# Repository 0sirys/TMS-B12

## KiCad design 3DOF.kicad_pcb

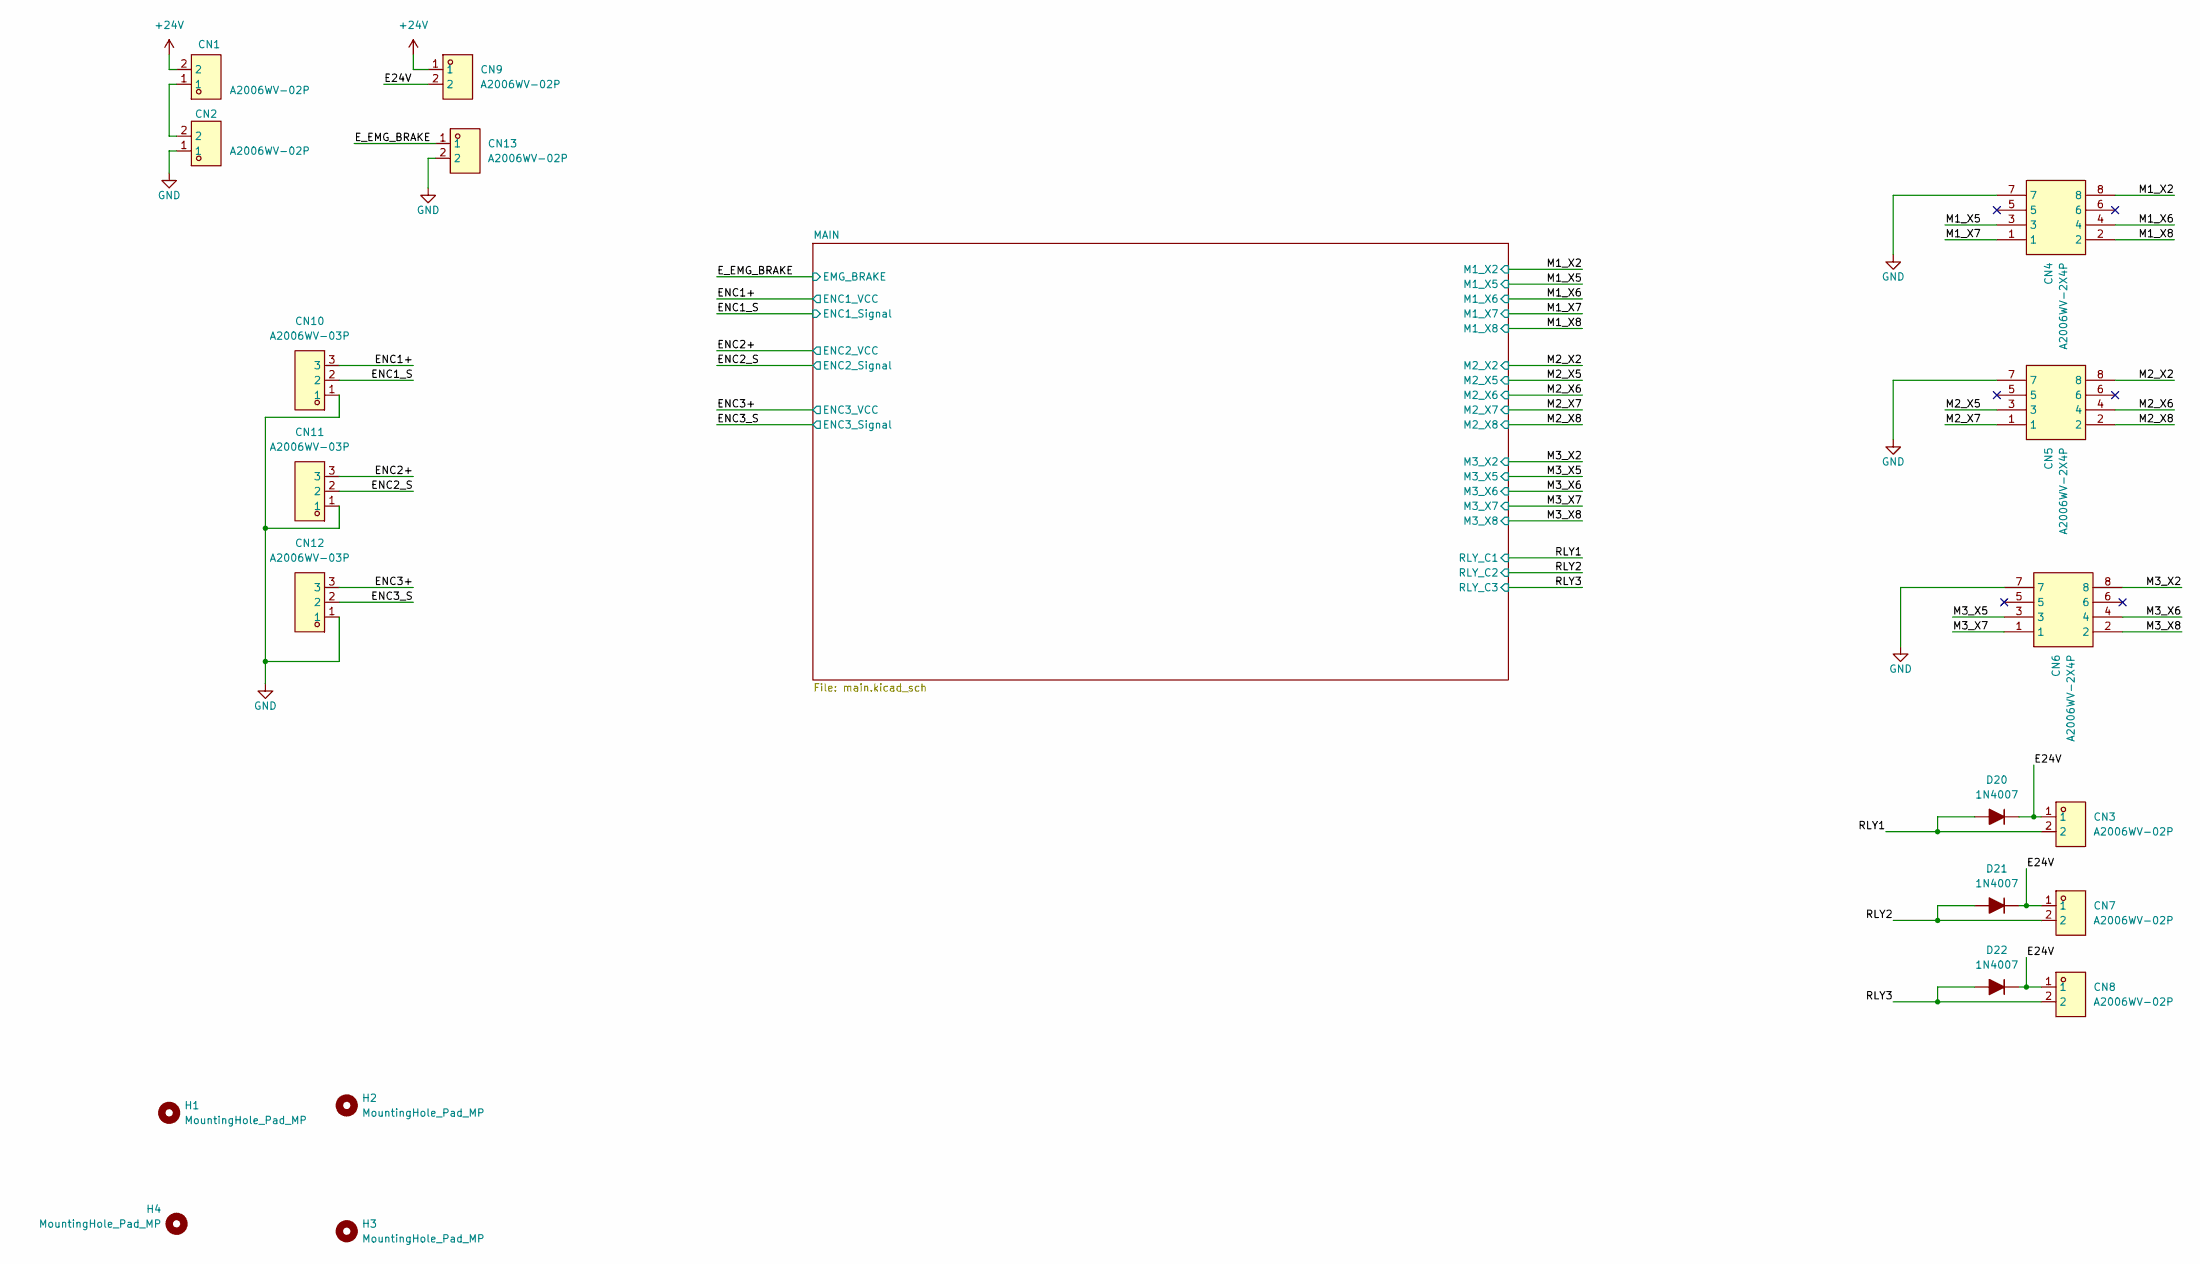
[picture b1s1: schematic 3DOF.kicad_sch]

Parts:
CN1, CN2, CN3, CN7, CN8, CN9, CN13: A2006WV-02P; CONN-TH_2P-P2.00_A2006WV-02P; MPN A2006WV-02P; LCSC Part C465363
CN4, CN5, CN6: A2006WV-2X4P; CONN-TH_A2006WV-2X4P; MPN A2006WV-2x4P; LCSC Part C225315
CN10, CN11, CN12: A2006WV-03P; CONN-TH_3P-P2.00_A2006WV-03P; MPN A2006WV-03P; LCSC Part C465364
D20, D21, D22: 1N4007; D_DO-41_SOD81_P7.62mm_Horizontal; LCSC Part C19357
H1, H2, H3, H4: MountingHole_Pad_MP; MountingHole_2.5mm

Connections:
+24V: CN1.2, CN9.1; also elsewhere on the board
/E24V: CN3.1, CN7.1, CN8.1, CN9.2, D20.1 (K), D21.1 (K), D22.1 (K)
/ENC1+: CN10.3; also elsewhere on the board
/ENC1_S: CN10.2; also elsewhere on the board
/ENC2+: CN11.3; also elsewhere on the board
/ENC2_S: CN11.2; also elsewhere on the board
/ENC3+: CN12.3; also elsewhere on the board
/ENC3_S: CN12.2; also elsewhere on the board
/E_EMG_BRAKE: CN13.1; also elsewhere on the board
/M1_X2: CN4.8; also elsewhere on the board
/M1_X5: CN4.3; also elsewhere on the board
/M1_X6: CN4.4; also elsewhere on the board
/M1_X7: CN4.1; also elsewhere on the board
/M1_X8: CN4.2; also elsewhere on the board
/M2_X2: CN5.8; also elsewhere on the board
/M2_X5: CN5.3; also elsewhere on the board
/M2_X6: CN5.4; also elsewhere on the board
/M2_X7: CN5.1; also elsewhere on the board
/M2_X8: CN5.2; also elsewhere on the board
/M3_X2: CN6.8; also elsewhere on the board
/M3_X5: CN6.3; also elsewhere on the board
/M3_X6: CN6.4; also elsewhere on the board
/M3_X7: CN6.1; also elsewhere on the board
/M3_X8: CN6.2; also elsewhere on the board
/RLY1: CN3.2, D20.2 (A); also elsewhere on the board
/RLY2: CN7.2, D21.2 (A); also elsewhere on the board
/RLY3: CN8.2, D22.2 (A); also elsewhere on the board
GND: CN2.1, CN4.7, CN5.7, CN6.7, CN10.1, CN11.1, CN12.1, CN13.2; also elsewhere on the board
unnamed: CN1.1, CN2.2

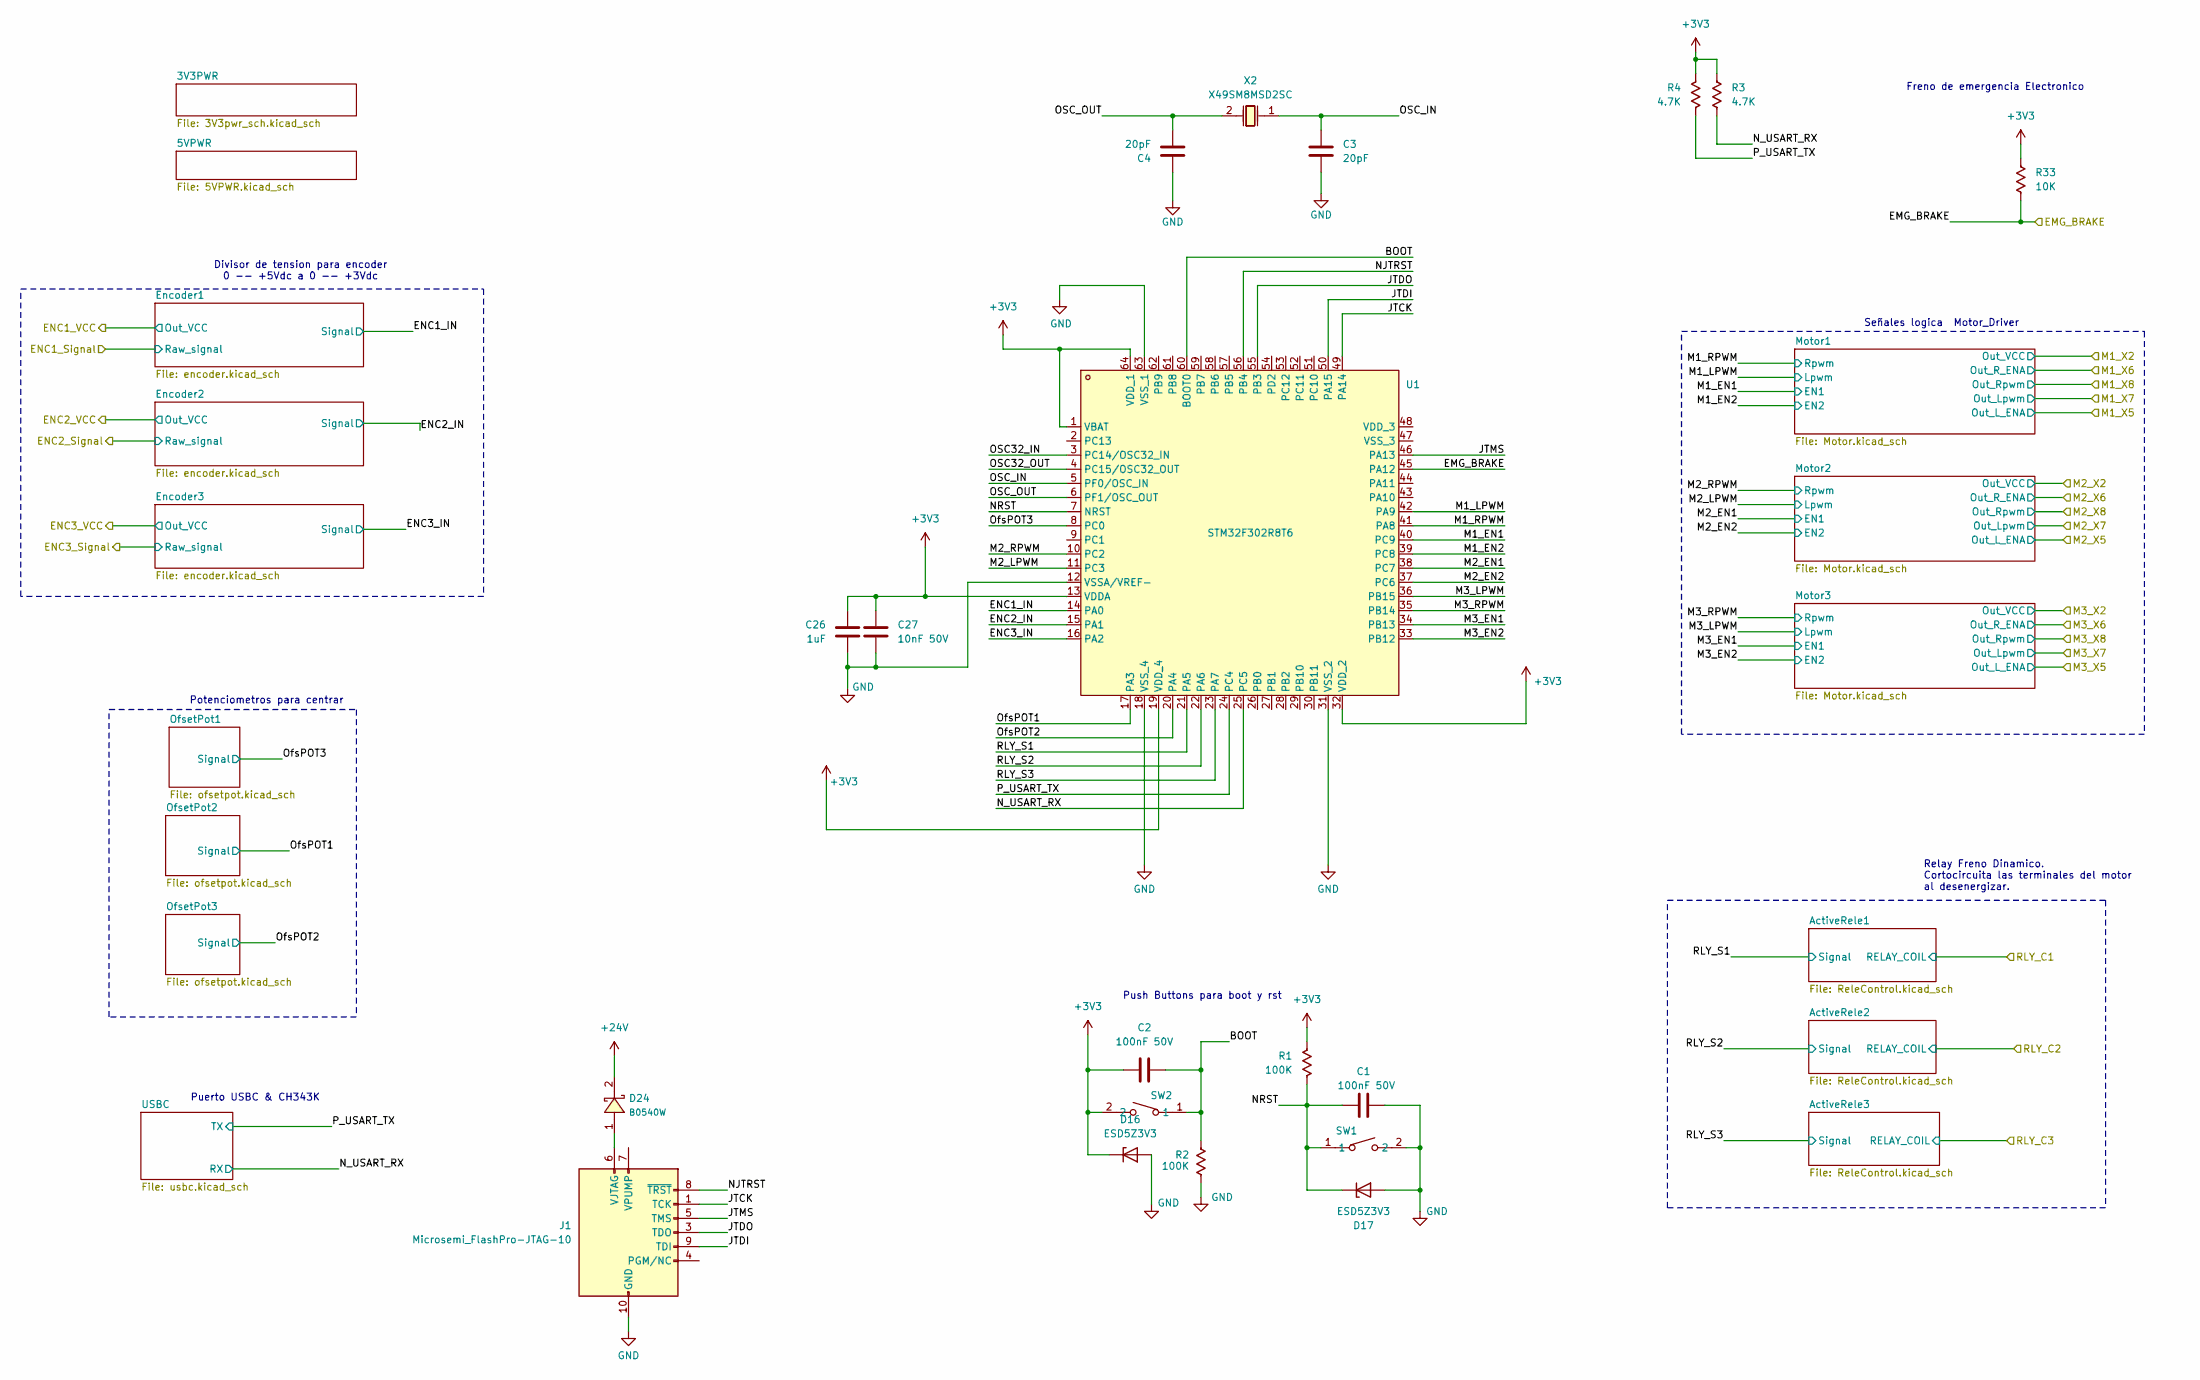
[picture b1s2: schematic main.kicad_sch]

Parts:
C1, C2: 100nF 50V; C_0402_1005Metric; LCSC Part C307331
C3, C4: 20pF; C_0402_1005Metric; LCSC Part C1554
C26: 1uF; C_0402_1005Metric; LCSC Part C52923
C27: 10nF 50V; C_0402_1005Metric; LCSC Part C1524
D16, D17: ESD5Z3V3; D_SOD-523; LCSC Part C502545
D24: B0540W; SOD-123_L2.7-W1.6-LS3.7-FD; MPN B0540W; LCSC Part C7420325
J1: Microsemi_FlashPro-JTAG-10; IDC-Header_2x05_P2.54mm_Vertical; LCSC Part C53207564
R1, R2: 100K; R_0402_1005Metric; LCSC Part C25741
R3, R4: 4.7K; R_0402_1005Metric; LCSC Part C25900
R33: 10K; R_0402_1005Metric; LCSC Part C25744
SW1, SW2: TS-1088-AR02016; SW-SMD_L3.9-W3.0-P4.45; MPN TS-1088-AR02016; LCSC Part C720477
U1: STM32F302R8T6; QFP-64_L10.0-W10.0-P0.50-LS12.0-BL; MPN STM32F302R8T6; LCSC Part C504601
X2: X49SM8MSD2SC; CRYSTAL-SMD_L11.5-W4.8-LS12.7; MPN X49SM8MSD2SC; LCSC Part C12674

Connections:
+3V3: C2.2, C26.1, C27.1, D16.1 (K), R1.1, R3.1, R4.1, R33.1, SW2.2, U1.1 (VBAT), U1.13 (VDDA), U1.19 (VDD_4), U1.32 (VDD_2), U1.64 (VDD_1); also elsewhere on the board
+24V: D24.2; also elsewhere on the board
/E_EMG_BRAKE: R33.2, U1.45 (PA12); also elsewhere on the board
/M1_X5: U1.39 (PC8); also elsewhere on the board
/M1_X6: U1.40 (PC9); also elsewhere on the board
/M1_X7: U1.42 (PA9); also elsewhere on the board
/M1_X8: U1.41 (PA8); also elsewhere on the board
/M2_X5: U1.37 (PC6); also elsewhere on the board
/M2_X6: U1.38 (PC7); also elsewhere on the board
/M2_X7: U1.11 (PC3); also elsewhere on the board
/M2_X8: U1.10 (PC2); also elsewhere on the board
/M3_X5: U1.33 (PB12); also elsewhere on the board
/M3_X6: U1.34 (PB13); also elsewhere on the board
/M3_X7: U1.36 (PB15); also elsewhere on the board
/M3_X8: U1.35 (PB14); also elsewhere on the board
/MAIN/BOOT: C2.1, R2.2, SW2.1, U1.60 (BOOT0)
/MAIN/ENC1_IN: U1.14 (PA0); also elsewhere on the board
/MAIN/ENC2_IN: U1.15 (PA1); also elsewhere on the board
/MAIN/ENC3_IN: U1.16 (PA2); also elsewhere on the board
/MAIN/JTCK: J1.1 (TCK), U1.49 (PA14)
/MAIN/JTDI: J1.9 (TDI), U1.50 (PA15)
/MAIN/JTDO: J1.3 (TDO), U1.55 (PB3)
/MAIN/JTMS: J1.5 (TMS), U1.46 (PA13)
/MAIN/NJTRST: J1.8 (~TRST), U1.56 (PB4)
/MAIN/NRST: C1.1, D17.1 (K), R1.2, SW1.1, U1.7 (NRST)
/MAIN/N_USART_RX: R3.2, U1.25 (PC5); also elsewhere on the board
/MAIN/OSC32_IN: U1.3 (PC14/OSC32_IN)
/MAIN/OSC32_OUT: U1.4 (PC15/OSC32_OUT)
/MAIN/OSC_IN: C3.2, U1.5 (PF0/OSC_IN), X2.1
/MAIN/OSC_OUT: C4.2, U1.6 (PF1/OSC_OUT), X2.2
/MAIN/OfsPOT1: U1.17 (PA3); also elsewhere on the board
/MAIN/OfsPOT2: U1.20 (PA4); also elsewhere on the board
/MAIN/OfsPOT3: U1.8 (PC0); also elsewhere on the board
/MAIN/P_USART_TX: R4.2, U1.24 (PC4); also elsewhere on the board
/MAIN/RLY_S1: U1.21 (PA5); also elsewhere on the board
/MAIN/RLY_S2: U1.22 (PA6); also elsewhere on the board
/MAIN/RLY_S3: U1.23 (PA7); also elsewhere on the board
GND: C1.2, C3.1, C4.1, C26.2, C27.2, D16.2 (A), D17.2 (A), J1.2 (GND), J1.10 (GND), R2.1, SW1.2, U1.12 (VSSA/VREF-), U1.18 (VSS_4), U1.31 (VSS_2), U1.63 (VSS_1); also elsewhere on the board
unnamed: D24.1, J1.6 (VJTAG)

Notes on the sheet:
Puerto USBC & CH343K
Potenciometros para centrar
Señales logica Motor_Driver
Divisor de tension para encoder 0 -- +5Vdc a 0 -- +3Vdc
Push Buttons para boot y rst
Freno de emergencia Electronico
Relay Freno Dinamico. Cortocircuita las terminales del motor al desenergizar.

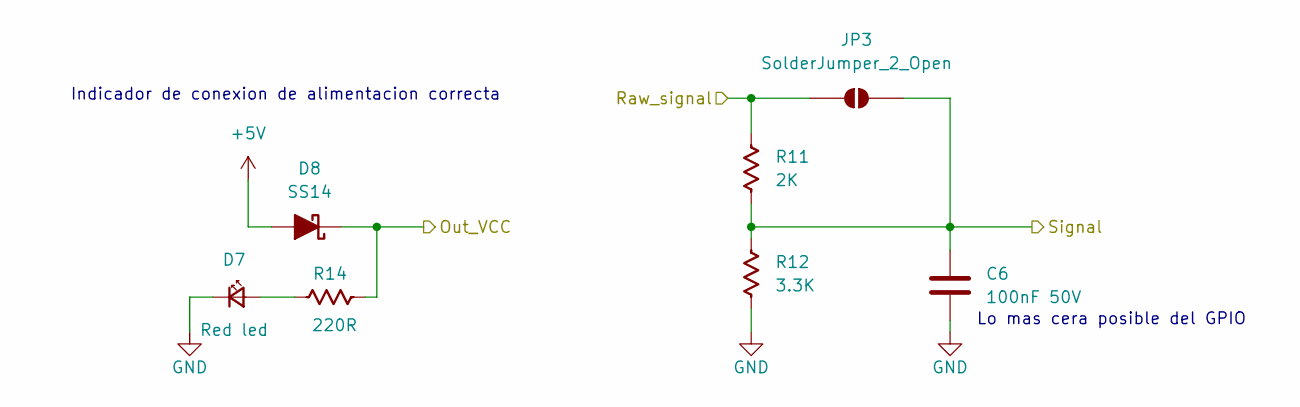
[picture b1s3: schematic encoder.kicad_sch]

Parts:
C6: 100nF 50V; C_0402_1005Metric; LCSC Part C307331
D7: Red led; LED_0603_1608Metric_Red; LCSC Part C2286
D8: SS14; D_SMA; LCSC Part C2480
JP3: SolderJumper_2_Open; SolderJumper-2_P1.3mm_Open_Pad1.0x1.5mm
R11: 2K; R_0402_1005Metric; LCSC Part C4109
R12: 3.3K; R_0402_1005Metric; LCSC Part C25890
R14: 220R; R_0402_1005Metric; LCSC Part C25091

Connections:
+5V: D8.2 (A); also elsewhere on the board
/ENC1+: D8.1 (K), R14.1; also elsewhere on the board
/ENC1_S: JP3.1 (A), R11.1; also elsewhere on the board
/MAIN/ENC1_IN: C6.1, JP3.2 (B), R11.2, R12.1; also elsewhere on the board
GND: C6.2, D7.1 (K), R12.2; also elsewhere on the board
unnamed: D7.2 (A), R14.2

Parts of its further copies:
C7, C11: 100nF 50V; C_0402_1005Metric; LCSC Part C307331
D9, D11: Red led; LED_0603_1608Metric_Red; LCSC Part C2286
D10, D12: SS14; D_SMA; LCSC Part C2480
JP2, JP4: SolderJumper_2_Open; SolderJumper-2_P1.3mm_Open_Pad1.0x1.5mm
R9, R10: 2K; R_0402_1005Metric; LCSC Part C4109
R13, R19: 3.3K; R_0402_1005Metric; LCSC Part C25890
R15, R16: 220R; R_0402_1005Metric; LCSC Part C25091

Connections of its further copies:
+5V: D10.2 (A), D12.2 (A); also elsewhere on the board
/ENC2+: D10.1 (K), R15.1; also elsewhere on the board
/ENC2_S: JP2.1 (A), R9.1; also elsewhere on the board
/ENC3+: D12.1 (K), R16.1; also elsewhere on the board
/ENC3_S: JP4.1 (A), R10.1; also elsewhere on the board
/MAIN/ENC2_IN: C7.1, JP2.2 (B), R9.2, R13.1; also elsewhere on the board
/MAIN/ENC3_IN: C11.1, JP4.2 (B), R10.2, R19.1; also elsewhere on the board
GND: C7.2, C11.2, D9.1 (K), D11.1 (K), R13.2, R19.2; also elsewhere on the board
unnamed: D9.2 (A), R15.2
unnamed: D11.2 (A), R16.2

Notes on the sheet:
Indicador de conexion de alimentacion correcta
Lo mas cera posible del GPIO

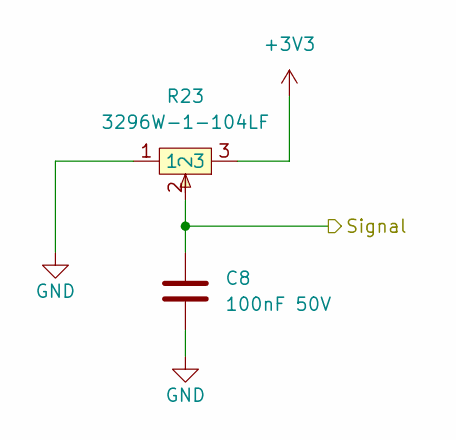
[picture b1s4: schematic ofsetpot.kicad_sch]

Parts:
C8: 100nF 50V; C_0402_1005Metric; LCSC Part C307331
R23: 3296W-1-104LF; RES-ADJ-TH_3296W; MPN 3296W-1-104LF; LCSC Part C48084

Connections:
+3V3: R23.3; also elsewhere on the board
/MAIN/OfsPOT3: C8.1, R23.2; also elsewhere on the board
GND: C8.2, R23.1; also elsewhere on the board

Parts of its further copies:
C9, C10: 100nF 50V; C_0402_1005Metric; LCSC Part C307331
R24, R25: 3296W-1-104LF; RES-ADJ-TH_3296W; MPN 3296W-1-104LF; LCSC Part C48084

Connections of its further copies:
+3V3: R24.3, R25.3; also elsewhere on the board
/MAIN/OfsPOT1: C9.1, R24.2; also elsewhere on the board
/MAIN/OfsPOT2: C10.1, R25.2; also elsewhere on the board
GND: C9.2, C10.2, R24.1, R25.1; also elsewhere on the board

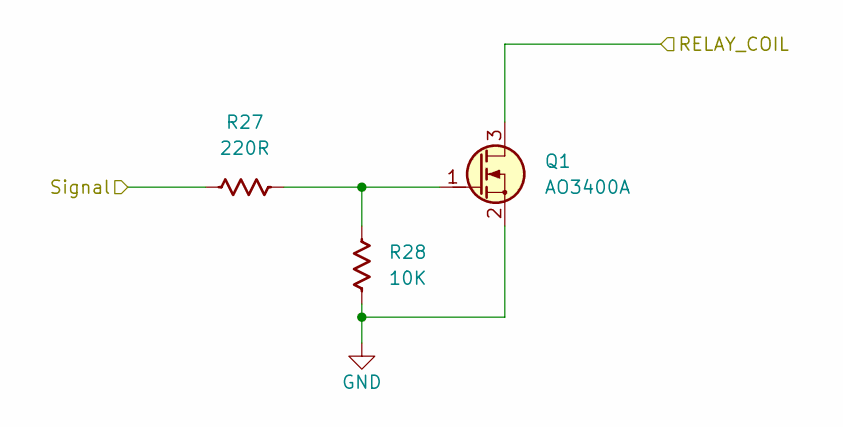
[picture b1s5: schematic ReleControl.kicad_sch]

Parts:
Q1: AO3400A; SOT-23; LCSC Part C20917
R27: 220R; R_0402_1005Metric; LCSC Part C25091
R28: 10K; R_0402_1005Metric; LCSC Part C25744

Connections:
/MAIN/RLY_S1: R27.1; also elsewhere on the board
/RLY1: Q1.3 (D); also elsewhere on the board
GND: Q1.2 (S), R28.1; also elsewhere on the board
unnamed: Q1.1 (G), R27.2, R28.2

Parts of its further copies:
Q2, Q3: AO3400A; SOT-23; LCSC Part C20917
R29, R31: 220R; R_0402_1005Metric; LCSC Part C25091
R30, R32: 10K; R_0402_1005Metric; LCSC Part C25744

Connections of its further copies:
/MAIN/RLY_S2: R29.1; also elsewhere on the board
/MAIN/RLY_S3: R31.1; also elsewhere on the board
/RLY2: Q2.3 (D); also elsewhere on the board
/RLY3: Q3.3 (D); also elsewhere on the board
GND: Q2.2 (S), Q3.2 (S), R30.1, R32.1; also elsewhere on the board
unnamed: Q2.1 (G), R29.2, R30.2
unnamed: Q3.1 (G), R31.2, R32.2

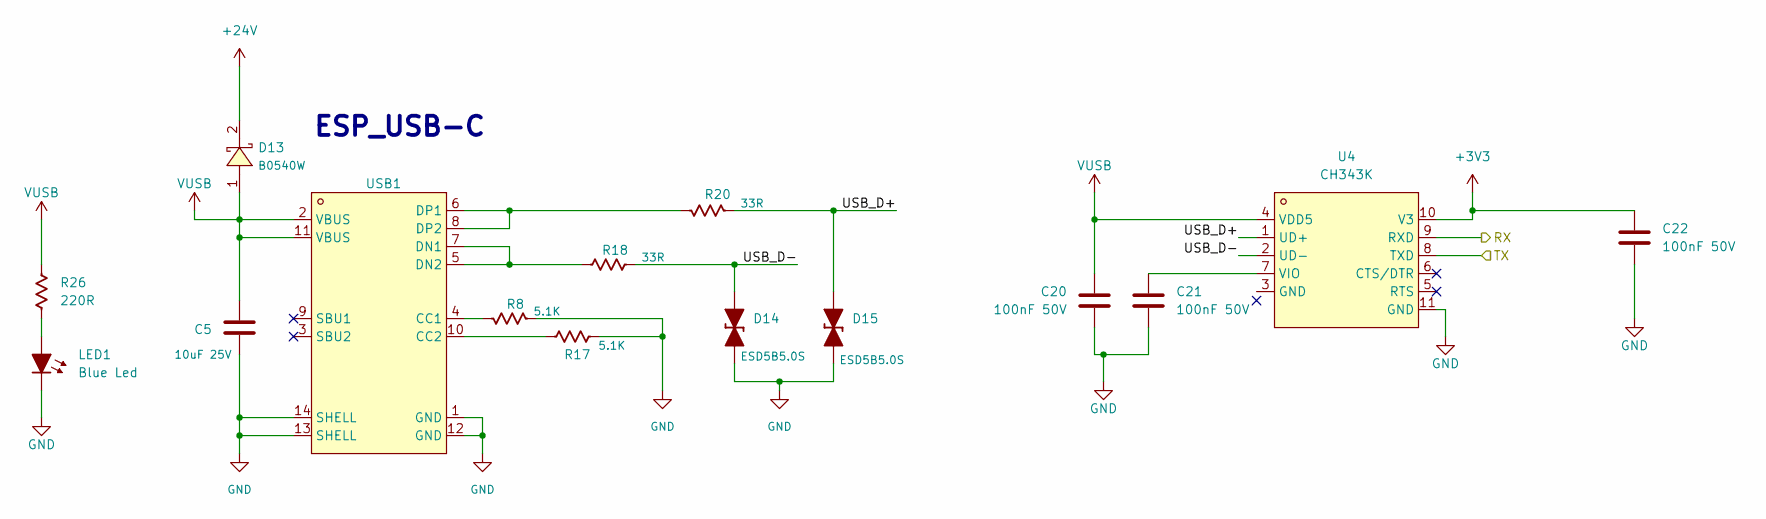
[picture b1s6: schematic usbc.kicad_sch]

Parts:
C5: 10uF 25V; C_0805_2012Metric; LCSC Part C15850
C20, C21, C22: 100nF 50V; C_0402_1005Metric; LCSC Part C307331
D13: B0540W; SOD-123_L2.7-W1.6-LS3.7-FD; MPN B0540W; LCSC Part C7420325
D14, D15: ESD5B5.0S; D_SOD-523; LCSC Part C93623
LED1: Blue Led; LED_0603_1608Metric; LCSC Part C2288
R8, R17: 5.1K; R_0402_1005Metric; LCSC Part C25905
R18, R20: 33R; R_0402_1005Metric; LCSC Part C25105
R26: 220R; R_0402_1005Metric; LCSC Part C25091
U4: CH343K; ESSOP-10_L4.9-W3.9-P1.0-LS6.0-TL-EP; MPN CH343K; LCSC Part C5832295
USB1: TYPE-C 16PIN 2MD; USB-C-SMD_TYPE-C-6PIN-2MD-073; MPN TYPE-C 16PIN 2MD(073); LCSC Part C2765186

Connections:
+3V3: C22.2, U4.10 (V3); also elsewhere on the board
+24V: D13.2; also elsewhere on the board
/MAIN/N_USART_RX: U4.9 (RXD); also elsewhere on the board
/MAIN/P_USART_TX: U4.8 (TXD); also elsewhere on the board
/MAIN/USBC/USB_D+: D15.2 (A), R20.2, U4.1 (UD+)
/MAIN/USBC/USB_D-: D14.2 (A), R18.2, U4.2 (UD-)
GND: C5.2, C20.2, C21.1, C22.1, D14.1 (K), D15.1 (K), LED1.1 (K), R8.2, R17.2, U4.11 (GND), USB1.1 (GND), USB1.12 (GND), USB1.13 (SHELL), USB1.14 (SHELL); also elsewhere on the board
unnamed: LED1.2 (A), R26.2
unnamed: C21.2, U4.7 (VIO)
unnamed: R8.1, USB1.4 (CC1)
unnamed: R17.1, USB1.10 (CC2)
unnamed: R18.1, USB1.5 (DN2), USB1.7 (DN1)
unnamed: R20.1, USB1.6 (DP1), USB1.8 (DP2)
VUSB: C5.1, C20.1, D13.1, R26.1, U4.4 (VDD5), USB1.2 (VBUS), USB1.11 (VBUS)

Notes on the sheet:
ESP_USB-C

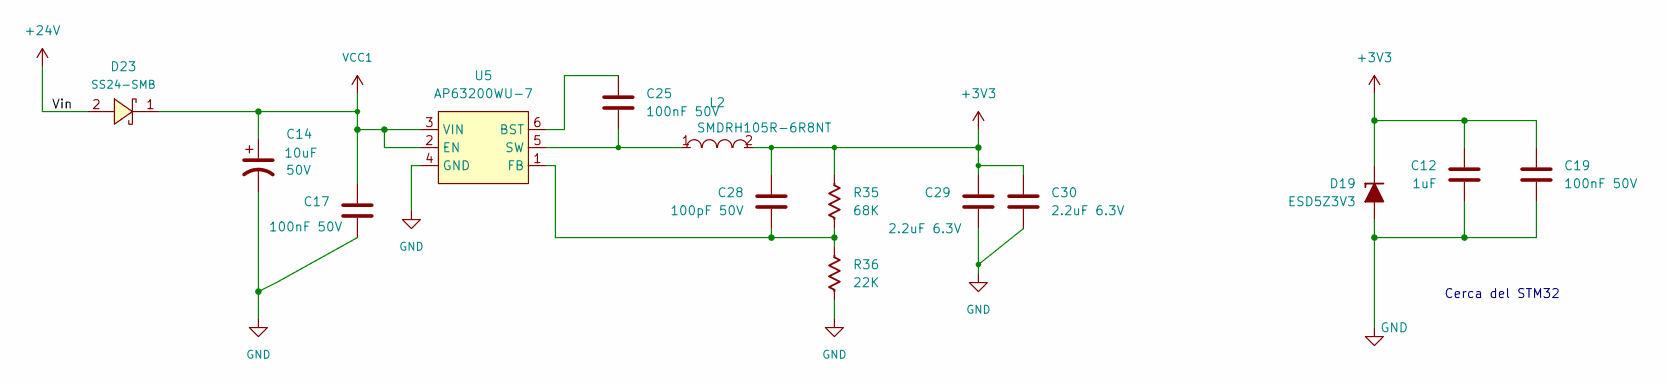
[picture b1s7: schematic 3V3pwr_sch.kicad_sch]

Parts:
C12: 1uF; C_0402_1005Metric; LCSC Part C52923
C14: 10uF; CP_Elec_6.3x5.4; Voltage 50V; Tolerance 100%; LCSC Part C970657
C17, C19, C25: 100nF 50V; C_0402_1005Metric; LCSC Part C307331
C28: 100pF 50V; C_0402_1005Metric; LCSC Part C1546
C29, C30: 2.2uF 6.3V; C_0402_1005Metric; LCSC Part C12530
D19: ESD5Z3V3; D_SOD-523; LCSC Part C502545
D23: SS24-SMB; SMB_L4.3-W3.6-LS5.3-RD; MPN SS24-SMB; LCSC Part C908683
L2: SMDRH105R-6R8NT; IND-SMD_L10.4-W10.3; MPN SMDRH105R-6R8NT; LCSC Part C10167
R35: 68K; R_0603_1608Metric; LCSC Part C23231
R36: 22K; R_0402_1005Metric; LCSC Part C25768
U5: AP63200WU-7; SOT-23-6_L2.9-W1.6-P0.95-LS2.8-BR; MPN AP63200WU-7; LCSC Part C2071868

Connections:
+3V3: C12.1, C19.1, C28.1, C29.1, C30.1, D19.1 (K), L2.2, R35.1; also elsewhere on the board
+24V: D23.2; also elsewhere on the board
GND: C12.2, C14.2, C17.1, C19.2, C29.2, C30.2, D19.2 (A), R36.2, U5.4 (GND); also elsewhere on the board
unnamed: C25.1, U5.6 (BST)
unnamed: C28.2, R35.2, R36.1, U5.1 (FB)
unnamed: C25.2, L2.1, U5.5 (SW)
VCC1: C14.1, C17.2, D23.1, U5.2 (EN), U5.3 (VIN)

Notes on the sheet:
Cerca del STM32

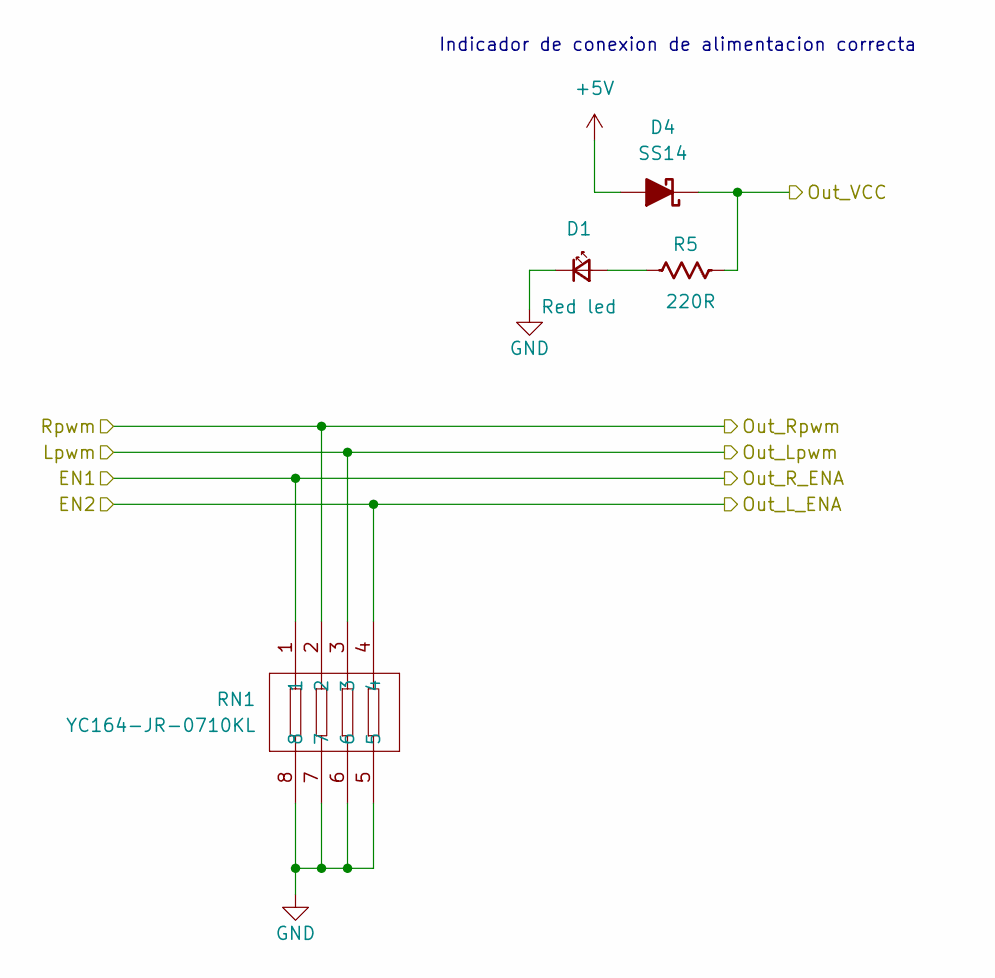
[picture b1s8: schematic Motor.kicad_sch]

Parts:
D1: Red led; LED_0603_1608Metric_Red; LCSC Part C2286
D4: SS14; D_SMA; LCSC Part C2480
R5: 220R; R_0402_1005Metric; LCSC Part C25091
RN1: YC164-JR-0710KL; RES-ARRAY-SMD_0603-8P-L3.2-W1.6-BL; MPN YC164-JR-0710KL; LCSC Part C107374

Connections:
+5V: D4.2 (A); also elsewhere on the board
/M1_X2: D4.1 (K), R5.1; also elsewhere on the board
/M1_X5: RN1.4; also elsewhere on the board
/M1_X6: RN1.1; also elsewhere on the board
/M1_X7: RN1.3; also elsewhere on the board
/M1_X8: RN1.2; also elsewhere on the board
GND: D1.1 (K), RN1.5, RN1.6, RN1.7, RN1.8; also elsewhere on the board
unnamed: D1.2 (A), R5.2

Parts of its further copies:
D2, D3: Red led; LED_0603_1608Metric_Red; LCSC Part C2286
D5, D6: SS14; D_SMA; LCSC Part C2480
R6, R7: 220R; R_0402_1005Metric; LCSC Part C25091
RN2, RN3: YC164-JR-0710KL; RES-ARRAY-SMD_0603-8P-L3.2-W1.6-BL; MPN YC164-JR-0710KL; LCSC Part C107374

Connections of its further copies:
+5V: D5.2 (A), D6.2 (A); also elsewhere on the board
/M2_X2: D5.1 (K), R6.1; also elsewhere on the board
/M2_X5: RN2.4; also elsewhere on the board
/M2_X6: RN2.1; also elsewhere on the board
/M2_X7: RN2.3; also elsewhere on the board
/M2_X8: RN2.2; also elsewhere on the board
/M3_X2: D6.1 (K), R7.1; also elsewhere on the board
/M3_X5: RN3.4; also elsewhere on the board
/M3_X6: RN3.1; also elsewhere on the board
/M3_X7: RN3.3; also elsewhere on the board
/M3_X8: RN3.2; also elsewhere on the board
GND: D2.1 (K), D3.1 (K), RN2.5, RN2.6, RN2.7, RN2.8, RN3.5, RN3.6, RN3.7, RN3.8; also elsewhere on the board
unnamed: D2.2 (A), R6.2
unnamed: D3.2 (A), R7.2

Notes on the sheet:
Indicador de conexion de alimentacion correcta

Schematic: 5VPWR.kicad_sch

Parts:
C13: 10uF; CP_Elec_6.3x5.4; Voltage 50V; Tolerance 100%; LCSC Part C970657
C15, C16: 100nF 50V; C_0402_1005Metric; LCSC Part C307331
C18, C23: 2.2uF 16V; C_0603_1608Metric; LCSC Part C23630
C24: 100pF 50V; C_0402_1005Metric; LCSC Part C1546
D18: SS24-SMB; SMB_L4.3-W3.6-LS5.3-RD; MPN SS24-SMB; LCSC Part C908683
L3: SMDRH105R-100MT; IND-SMD_L10.4-W10.3; MPN SMDRH105R-100MT; LCSC Part C9185
R34: 13K; R_0603_1608Metric; LCSC Part C22797
R37: 68K; R_0603_1608Metric; LCSC Part C23231
U3: AP63200WU-7; SOT-23-6_L2.9-W1.6-P0.95-LS2.8-BR; MPN AP63200WU-7; LCSC Part C2071868

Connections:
+5V: C18.1, C23.1, C24.1, L3.2, R37.1; also elsewhere on the board
+24V: D18.2; also elsewhere on the board
GND: C13.2, C15.1, C18.2, C23.2, R34.2, U3.4 (GND); also elsewhere on the board
unnamed: C16.1, U3.6 (BST)
unnamed: C24.2, R34.1, R37.2, U3.1 (FB)
unnamed: C16.2, L3.1, U3.5 (SW)
VCC2: C13.1, C15.2, D18.1, U3.2 (EN), U3.3 (VIN)

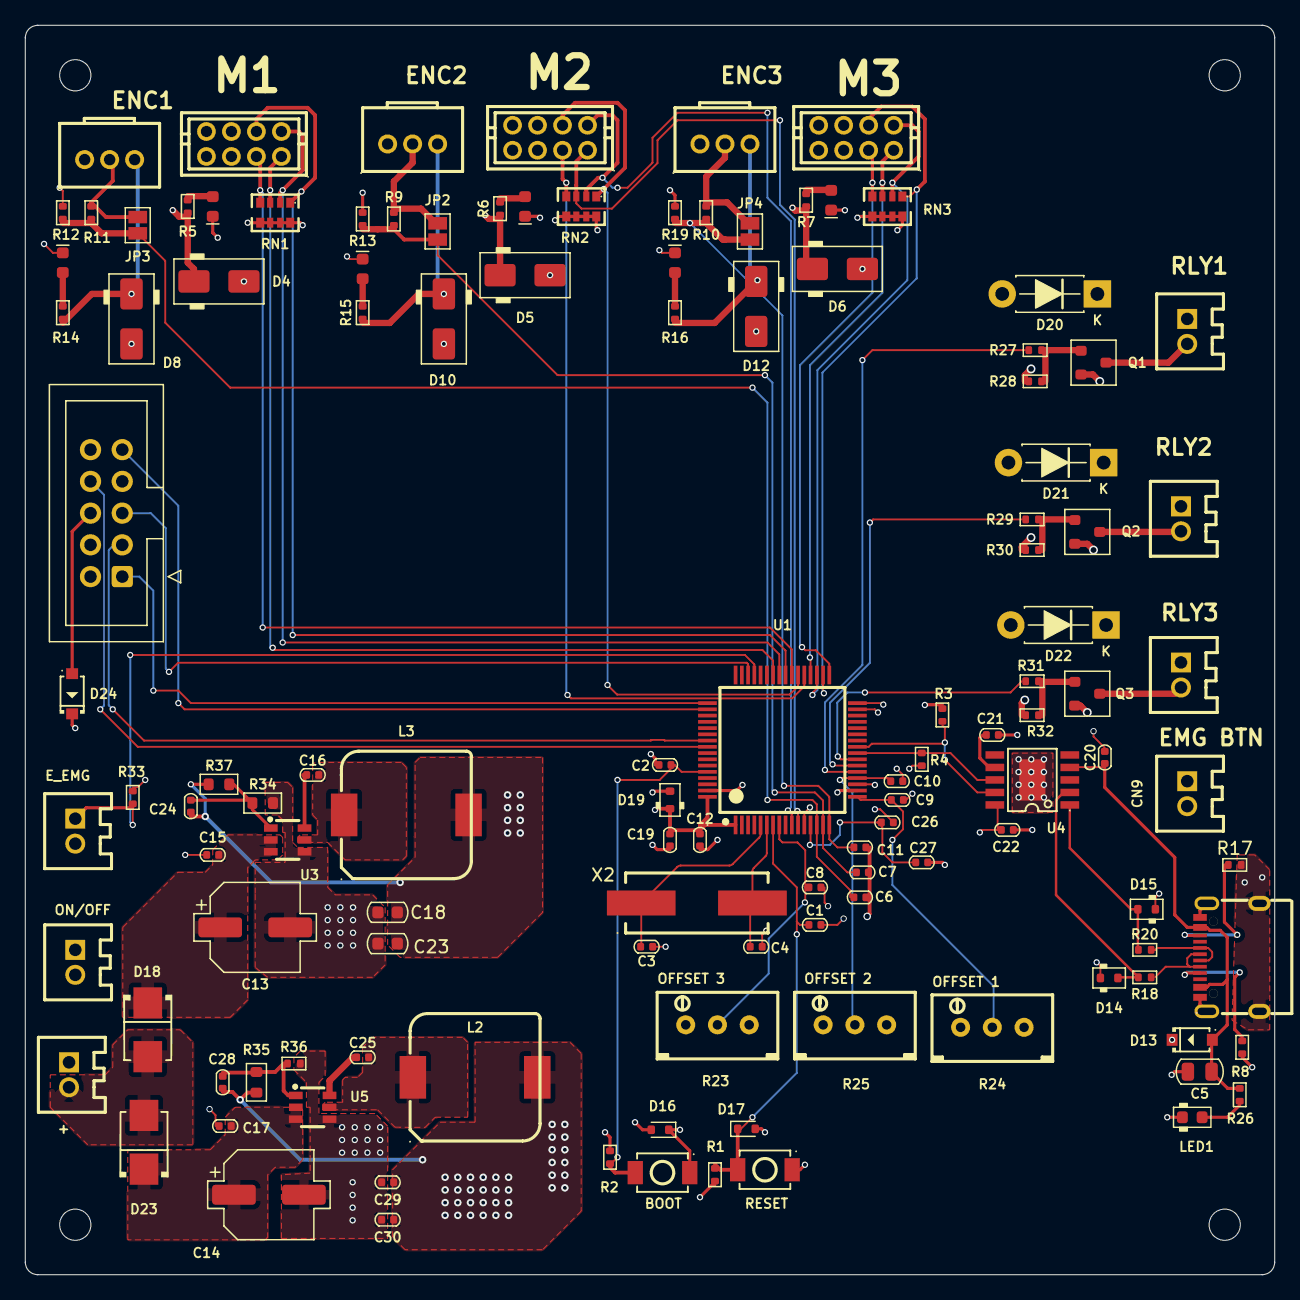
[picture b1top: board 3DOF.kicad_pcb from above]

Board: 4 copper layers, 100.0 x 100.0 mm, 127 parts (0 on the bottom side), 78 nets.

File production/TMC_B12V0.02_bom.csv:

Designator,Footprint,Quantity,Value,LCSC Part #
"C1, C10, C11, C15, C16, C17, C19, C2, C20, C21, C22, C25, C6, C7, C8, C9",0402,16,100nF 50V,C307331
"C12, C26",0402,2,1uF,C52923
"C13, C14",CP_Elec_6.3x5.4,2,10uF,C970657
"C18, C23",0603,2,2.2uF 16V,C23630
"C24, C28",0402,2,100pF 50V,C1546
C27,0402,1,10nF 50V,C1524
"C29, C30",0402,2,2.2uF 6.3V,C12530
"C3, C4",0402,2,20pF,C1554
C5,0805,1,10uF 25V,C15850
"CN1, CN13, CN2, CN3, CN7, CN8, CN9",CONN-TH_2P-P2.00_A2006WV-02P,7,A2006WV-02P,C465363
"CN10, CN11, CN12",CONN-TH_3P-P2.00_A2006WV-03P,3,A2006WV-03P,C465364
"CN4, CN5, CN6",CONN-TH_A2006WV-2X4P,3,A2006WV-2X4P,C225315
"D1, D11, D2, D3, D7, D9",0603,6,Red led,C2286
"D10, D12, D4, D5, D6, D8",D_SMA,6,SS14,C2480
"D13, D24",SOD-123_L2.7-W1.6-LS3.7-FD,2,B0540W,C7420325
"D14, D15",D_SOD-523,2,ESD5B5.0S,C93623
"D16, D17, D19",D_SOD-523,3,ESD5Z3V3,C502545
"D18, D23",SMB_L4.3-W3.6-LS5.3-RD,2,SS24-SMB,C908683
J1,IDC-Header_2x05_P2.54mm_Vertical,1,Microsemi_FlashPro-JTAG-10,C53207564
L2,IND-SMD_L10.4-W10.3,1,SMDRH105R-6R8NT,C10167
L3,IND-SMD_L10.4-W10.3,1,SMDRH105R-100MT,C9185
LED1,0603,1,Blue Led,C2288
"Q1, Q2, Q3",SOT-23,3,AO3400A,C20917
"R1, R2",0402,2,100K,C25741
"R10, R11, R9",0402,3,2K,C4109
"R12, R13, R19",0402,3,3.3K,C25890
"R14, R15, R16, R26, R27, R29, R31, R5, R6, R7",0402,10,220R,C25091
"R17, R8",0402,2,5.1K,C25905
"R18, R20",0402,2,33R,C25105
"R23, R24, R25",RES-ADJ-TH_3296W,3,3296W-1-104LF,C48084
"R28, R30, R32, R33",0402,4,10K,C25744
"R3, R4",0402,2,4.7K,C25900
R34,0603,1,13K,C22797
"R35, R37",0603,2,68K,C23231
R36,0402,1,22K,C25768
"RN1, RN2, RN3",RES-ARRAY-SMD_0603-8P-L3.2-W1.6-BL,3,YC164-JR-0710KL,C107374
"SW1, SW2",SW-SMD_L3.9-W3.0-P4.45,2,TS-1088-AR02016,C720477
U1,QFP-64_L10.0-W10.0-P0.50-LS12.0-BL,1,STM32F302R8T6,C504601
"U3, U5",SOT-23-6_L2.9-W1.6-P0.95-LS2.8-BR,2,AP63200WU-7,C2071868
U4,ESSOP-10_L4.9-W3.9-P1.0-LS6.0-TL-EP,1,CH343K,C5832295
USB1,USB-C-SMD_TYPE-C-6PIN-2MD-073,1,TYPE-C 16PIN 2MD,C2765186
X2,CRYSTAL-SMD_L11.5-W4.8-LS12.7,1,X49SM8MSD2SC,C12674
